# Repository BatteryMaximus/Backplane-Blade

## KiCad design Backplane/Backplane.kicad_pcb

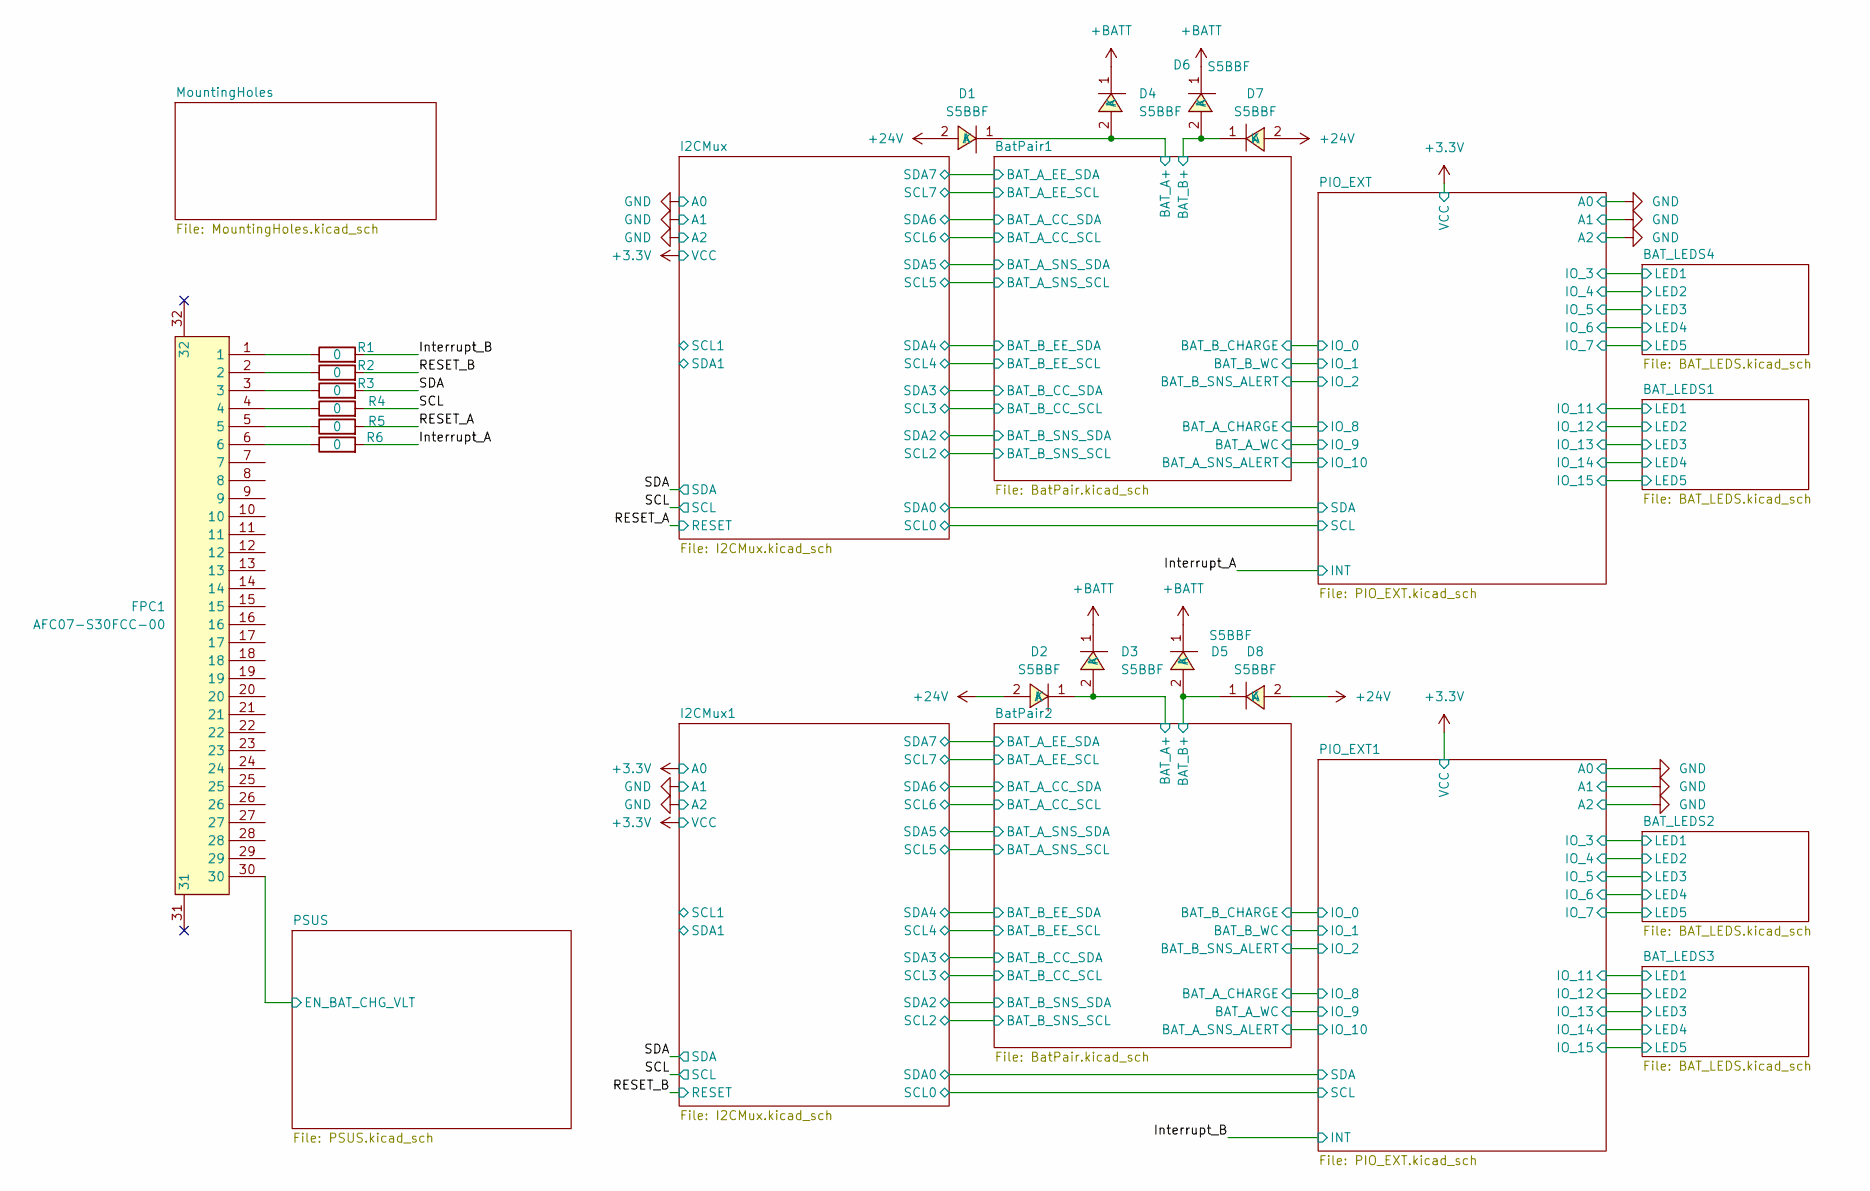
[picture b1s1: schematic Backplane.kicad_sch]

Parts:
D1, D2, D3, D4, D5, D6, D7, D8: S5BBF; SMBF_L4.3-W3.6-LS5.3-RD; LCSC Part C475750
FPC1: AFC07-S30FCC-00; FPC-SMD_P0.50-30P_LCSXJ-H2.0; LCSC Part C262218
R1, R2, R3, R4, R5, R6: 0; R_1206_3216Metric_Pad1.30x1.75mm_HandSolder

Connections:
+24V: D1.2 (A), D2.2 (A), D7.2 (A), D8.2 (A); also elsewhere on the board
+BATT: D3.1 (K), D4.1 (K), D5.1 (K), D6.1 (K); also elsewhere on the board
/BatPair1/BatMax - Female1/P+: D6.2 (A), D7.1 (K); also elsewhere on the board
/BatPair1/BatMax - Female/P+: D1.1 (K), D4.2 (A); also elsewhere on the board
/BatPair2/BatMax - Female1/P+: D5.2 (A), D8.1 (K); also elsewhere on the board
/BatPair2/BatMax - Female/P+: D2.1 (K), D3.2 (A); also elsewhere on the board
/Interrupt_A: R6.2; also elsewhere on the board
/Interrupt_B: R1.2; also elsewhere on the board
/PSUS/EN_BAT_CHG_VLT: FPC1.30; also elsewhere on the board
/RESET_A: R5.2; also elsewhere on the board
/RESET_B: R2.2; also elsewhere on the board
/SCL: R4.2; also elsewhere on the board
/SDA: R3.2; also elsewhere on the board
unnamed: FPC1.1, R1.1
unnamed: FPC1.2, R2.1
unnamed: FPC1.3, R3.1
unnamed: FPC1.4, R4.1
unnamed: FPC1.5, R5.1
unnamed: FPC1.6, R6.1

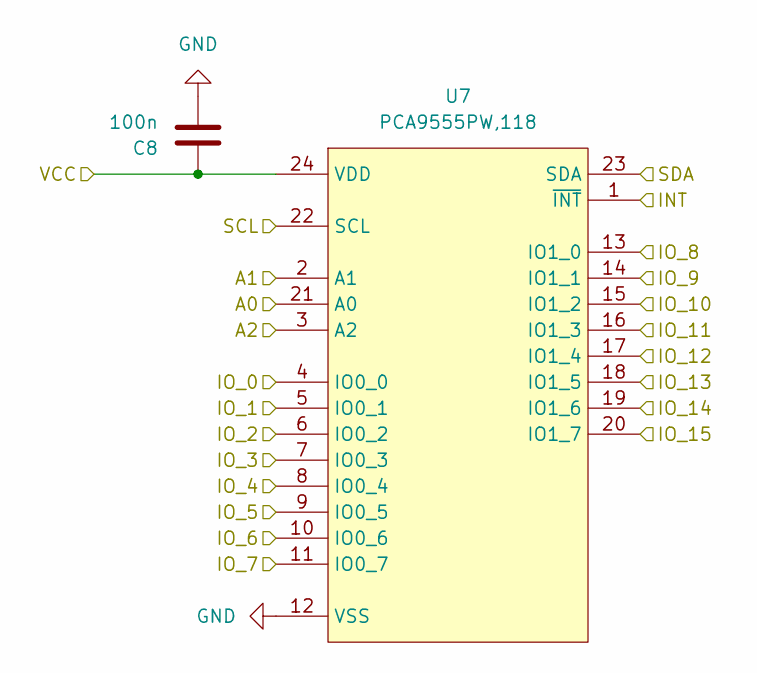
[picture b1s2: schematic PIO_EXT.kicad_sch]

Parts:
C8: 100n; R_1206_3216Metric_Pad1.30x1.75mm_HandSolder
U7: PCA9555PW,118; TSSOP-24_L7.8-W4.4-P0.65-LS6.4-BL; LCSC Part C128392

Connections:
+3.3V: C8.1, U7.24 (VDD); also elsewhere on the board
/BAT_LEDS1/LED1: U7.16 (IO1_3); also elsewhere on the board
/BAT_LEDS1/LED2: U7.17 (IO1_4); also elsewhere on the board
/BAT_LEDS1/LED3: U7.18 (IO1_5); also elsewhere on the board
/BAT_LEDS1/LED4: U7.19 (IO1_6); also elsewhere on the board
/BAT_LEDS1/LED5: U7.20 (IO1_7); also elsewhere on the board
/BAT_LEDS4/LED1: U7.7 (IO0_3); also elsewhere on the board
/BAT_LEDS4/LED2: U7.8 (IO0_4); also elsewhere on the board
/BAT_LEDS4/LED3: U7.9 (IO0_5); also elsewhere on the board
/BAT_LEDS4/LED4: U7.10 (IO0_6); also elsewhere on the board
/BAT_LEDS4/LED5: U7.11 (IO0_7); also elsewhere on the board
/BatPair1/BAT_A_CHARGE: U7.13 (IO1_0); also elsewhere on the board
/BatPair1/BAT_A_SNS_ALERT: U7.15 (IO1_2); also elsewhere on the board
/BatPair1/BAT_B_CHARGE: U7.4 (IO0_0); also elsewhere on the board
/BatPair1/BAT_B_SNS_ALERT: U7.6 (IO0_2); also elsewhere on the board
/BatPair1/BatMax - Female1/EEPROM_WC: U7.5 (IO0_1); also elsewhere on the board
/BatPair1/BatMax - Female/EEPROM_WC: U7.14 (IO1_1); also elsewhere on the board
/I2CMux/SCL0: U7.22 (SCL); also elsewhere on the board
/I2CMux/SDA0: U7.23 (SDA); also elsewhere on the board
/Interrupt_A: U7.1 (~INT); also elsewhere on the board
GND: C8.2, U7.2 (A1), U7.3 (A2), U7.12 (VSS), U7.21 (A0); also elsewhere on the board

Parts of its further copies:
C22: 100n; R_1206_3216Metric_Pad1.30x1.75mm_HandSolder
U20: PCA9555PW,118; TSSOP-24_L7.8-W4.4-P0.65-LS6.4-BL; LCSC Part C128392

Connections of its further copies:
+3.3V: C22.1, U20.24 (VDD); also elsewhere on the board
/BAT_LEDS2/LED1: U20.7 (IO0_3); also elsewhere on the board
/BAT_LEDS2/LED2: U20.8 (IO0_4); also elsewhere on the board
/BAT_LEDS2/LED3: U20.9 (IO0_5); also elsewhere on the board
/BAT_LEDS2/LED4: U20.10 (IO0_6); also elsewhere on the board
/BAT_LEDS2/LED5: U20.11 (IO0_7); also elsewhere on the board
/BAT_LEDS3/LED1: U20.16 (IO1_3); also elsewhere on the board
/BAT_LEDS3/LED2: U20.17 (IO1_4); also elsewhere on the board
/BAT_LEDS3/LED3: U20.18 (IO1_5); also elsewhere on the board
/BAT_LEDS3/LED4: U20.19 (IO1_6); also elsewhere on the board
/BAT_LEDS3/LED5: U20.20 (IO1_7); also elsewhere on the board
/BatPair2/BAT_A_CHARGE: U20.13 (IO1_0); also elsewhere on the board
/BatPair2/BAT_A_SNS_ALERT: U20.15 (IO1_2); also elsewhere on the board
/BatPair2/BAT_B_CHARGE: U20.4 (IO0_0); also elsewhere on the board
/BatPair2/BAT_B_SNS_ALERT: U20.6 (IO0_2); also elsewhere on the board
/BatPair2/BatMax - Female1/EEPROM_WC: U20.5 (IO0_1); also elsewhere on the board
/BatPair2/BatMax - Female/EEPROM_WC: U20.14 (IO1_1); also elsewhere on the board
/I2CMux1/SCL0: U20.22 (SCL); also elsewhere on the board
/I2CMux1/SDA0: U20.23 (SDA); also elsewhere on the board
/Interrupt_B: U20.1 (~INT); also elsewhere on the board
GND: C22.2, U20.2 (A1), U20.3 (A2), U20.12 (VSS), U20.21 (A0); also elsewhere on the board

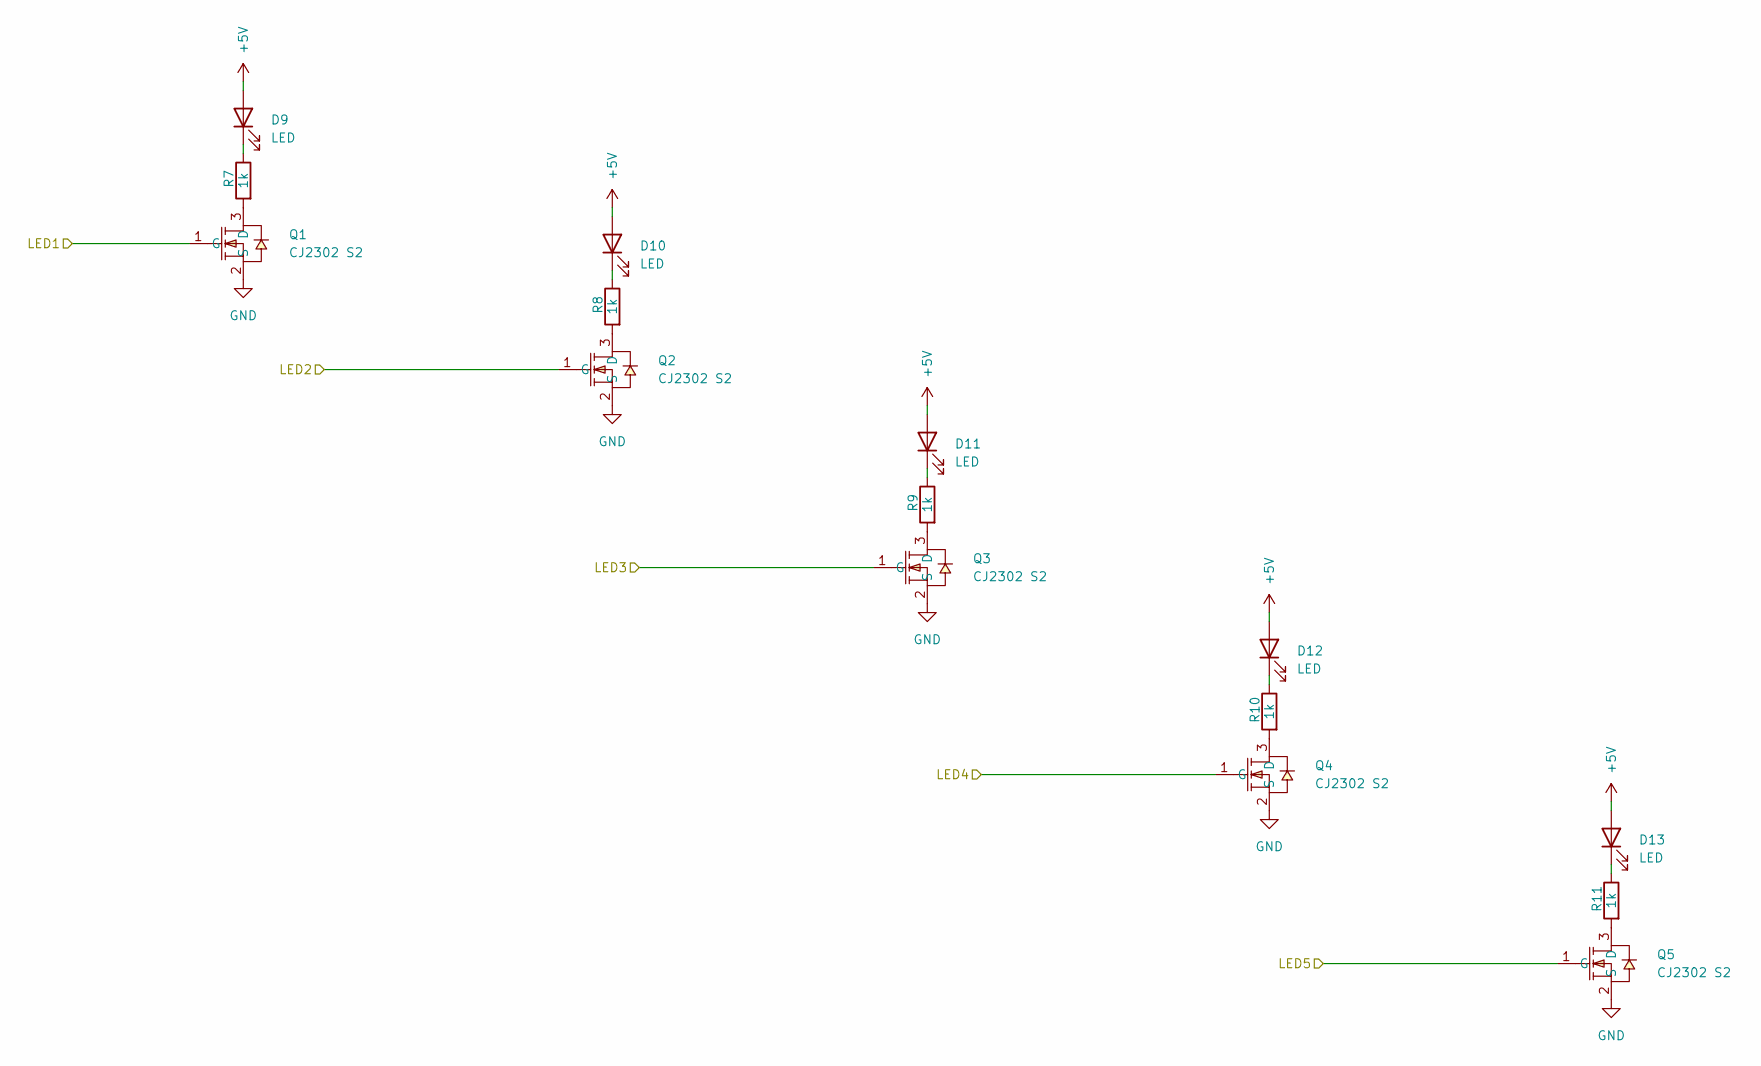
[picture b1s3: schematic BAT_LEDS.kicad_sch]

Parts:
D9, D10, D11, D12, D13: LED; LED_1206_3216Metric
Q1, Q2, Q3, Q4, Q5: CJ2302 S2; SOT-23-3_L3.0-W1.7-P0.95-LS2.9-BR; LCSC Part C8548
R7, R8, R9, R10, R11: 1k; R_1206_3216Metric_Pad1.30x1.75mm_HandSolder

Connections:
+5V: D9.2 (A), D10.2 (A), D11.2 (A), D12.2 (A), D13.2 (A); also elsewhere on the board
/BAT_LEDS1/LED1: Q1.1 (G); also elsewhere on the board
/BAT_LEDS1/LED2: Q2.1 (G); also elsewhere on the board
/BAT_LEDS1/LED3: Q3.1 (G); also elsewhere on the board
/BAT_LEDS1/LED4: Q4.1 (G); also elsewhere on the board
/BAT_LEDS1/LED5: Q5.1 (G); also elsewhere on the board
GND: Q1.2 (S), Q2.2 (S), Q3.2 (S), Q4.2 (S), Q5.2 (S); also elsewhere on the board
unnamed: D9.1 (K), R7.1
unnamed: D10.1 (K), R8.1
unnamed: D11.1 (K), R9.1
unnamed: D12.1 (K), R10.1
unnamed: D13.1 (K), R11.1
unnamed: Q1.3 (D), R7.2
unnamed: Q2.3 (D), R8.2
unnamed: Q3.3 (D), R9.2
unnamed: Q4.3 (D), R10.2
unnamed: Q5.3 (D), R11.2

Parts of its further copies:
D14, D15, D16, D17, D18, D19, D20, D21, D22, D23, D24, D25, D26, D27, D28: LED; LED_1206_3216Metric
Q6, Q7, Q8, Q9, Q10, Q11, Q12, Q13, Q14, Q15, Q18, Q19, Q20, Q21, Q22: CJ2302 S2; SOT-23-3_L3.0-W1.7-P0.95-LS2.9-BR; LCSC Part C8548
R12, R13, R14, R15, R16, R17, R18, R19, R20, R21, R48, R49, R50, R51, R52: 1k; R_1206_3216Metric_Pad1.30x1.75mm_HandSolder

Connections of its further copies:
+5V: D14.2 (A), D15.2 (A), D16.2 (A), D17.2 (A), D18.2 (A), D19.2 (A), D20.2 (A), D21.2 (A), D22.2 (A), D23.2 (A), D24.2 (A), D25.2 (A), D26.2 (A), D27.2 (A), D28.2 (A); also elsewhere on the board
/BAT_LEDS2/LED1: Q6.1 (G); also elsewhere on the board
/BAT_LEDS2/LED2: Q7.1 (G); also elsewhere on the board
/BAT_LEDS2/LED3: Q8.1 (G); also elsewhere on the board
/BAT_LEDS2/LED4: Q9.1 (G); also elsewhere on the board
/BAT_LEDS2/LED5: Q10.1 (G); also elsewhere on the board
/BAT_LEDS3/LED1: Q11.1 (G); also elsewhere on the board
/BAT_LEDS3/LED2: Q12.1 (G); also elsewhere on the board
/BAT_LEDS3/LED3: Q13.1 (G); also elsewhere on the board
/BAT_LEDS3/LED4: Q14.1 (G); also elsewhere on the board
/BAT_LEDS3/LED5: Q15.1 (G); also elsewhere on the board
/BAT_LEDS4/LED1: Q18.1 (G); also elsewhere on the board
/BAT_LEDS4/LED2: Q19.1 (G); also elsewhere on the board
/BAT_LEDS4/LED3: Q20.1 (G); also elsewhere on the board
/BAT_LEDS4/LED4: Q21.1 (G); also elsewhere on the board
/BAT_LEDS4/LED5: Q22.1 (G); also elsewhere on the board
GND: Q6.2 (S), Q7.2 (S), Q8.2 (S), Q9.2 (S), Q10.2 (S), Q11.2 (S), Q12.2 (S), Q13.2 (S), Q14.2 (S), Q15.2 (S), Q18.2 (S), Q19.2 (S), Q20.2 (S), Q21.2 (S), Q22.2 (S); also elsewhere on the board
unnamed: D14.1 (K), R12.1
unnamed: D15.1 (K), R13.1
unnamed: D16.1 (K), R14.1
unnamed: D17.1 (K), R15.1
unnamed: D18.1 (K), R16.1
unnamed: D19.1 (K), R17.1
unnamed: D20.1 (K), R18.1
unnamed: D21.1 (K), R19.1
unnamed: D22.1 (K), R20.1
unnamed: D23.1 (K), R21.1
unnamed: D24.1 (K), R48.1
unnamed: D25.1 (K), R49.1
unnamed: D26.1 (K), R50.1
unnamed: D27.1 (K), R51.1
unnamed: D28.1 (K), R52.1
unnamed: Q6.3 (D), R12.2
unnamed: Q7.3 (D), R13.2
unnamed: Q8.3 (D), R14.2
unnamed: Q9.3 (D), R15.2
unnamed: Q10.3 (D), R16.2
unnamed: Q11.3 (D), R17.2
unnamed: Q12.3 (D), R18.2
unnamed: Q13.3 (D), R19.2
unnamed: Q14.3 (D), R20.2
unnamed: Q15.3 (D), R21.2
unnamed: Q18.3 (D), R48.2
unnamed: Q19.3 (D), R49.2
unnamed: Q20.3 (D), R50.2
unnamed: Q21.3 (D), R51.2
unnamed: Q22.3 (D), R52.2

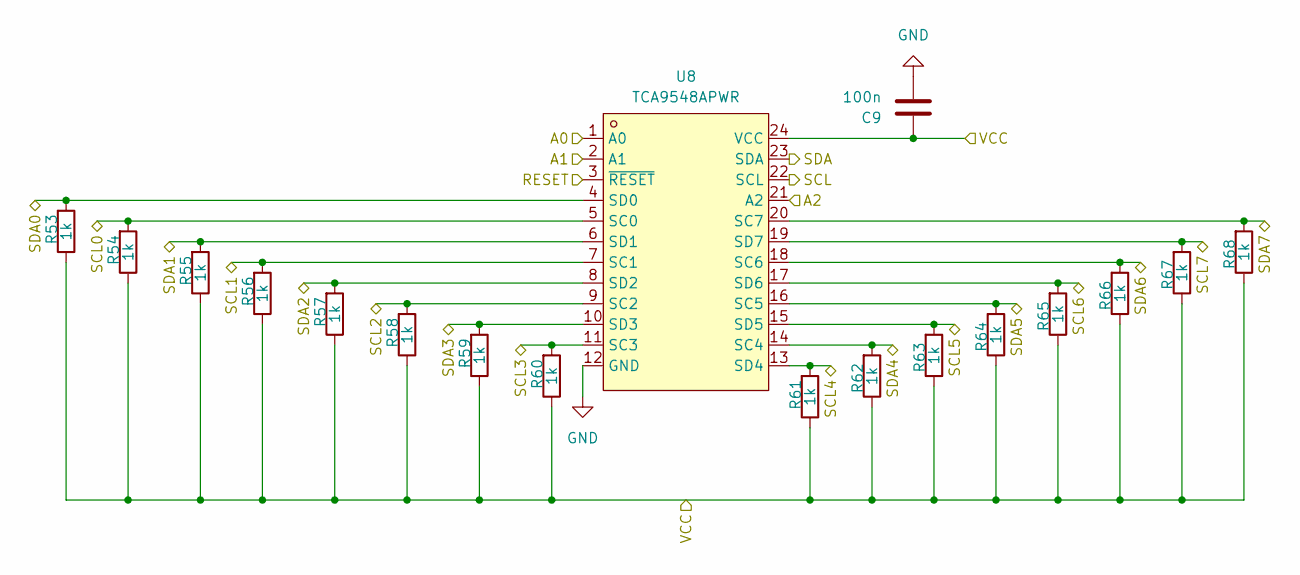
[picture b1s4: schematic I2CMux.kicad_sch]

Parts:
C9: 100n; R_1206_3216Metric_Pad1.30x1.75mm_HandSolder
R53, R54, R55, R56, R57, R58, R59, R60, R61, R62, R63, R64, R65, R66, R67, R68: 1k; R_1206_3216Metric_Pad1.30x1.75mm_HandSolder
U8: TCA9548APWR; TSSOP-24_L7.8-W4.4-P0.65-LS6.4-BL; LCSC Part C130026

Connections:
+3.3V: C9.1, R53.1, R54.1, R55.1, R56.1, R57.1, R58.1, R59.1, R60.1, R61.1, R62.1, R63.1, R64.1, R65.1, R66.1, R67.1, R68.1, U8.24 (VCC); also elsewhere on the board
/BatPair1/BAT_A_CC_SCL: R65.2, U8.17 (SD6); also elsewhere on the board
/BatPair1/BAT_A_CC_SDA: R66.2, U8.18 (SC6); also elsewhere on the board
/BatPair1/BAT_A_SNS_SCL: R63.2, U8.15 (SD5); also elsewhere on the board
/BatPair1/BAT_A_SNS_SDA: R64.2, U8.16 (SC5); also elsewhere on the board
/BatPair1/BAT_B_CC_SCL: R60.2, U8.11 (SC3); also elsewhere on the board
/BatPair1/BAT_B_CC_SDA: R59.2, U8.10 (SD3); also elsewhere on the board
/BatPair1/BAT_B_SNS_SCL: R58.2, U8.9 (SC2); also elsewhere on the board
/BatPair1/BAT_B_SNS_SDA: R57.2, U8.8 (SD2); also elsewhere on the board
/BatPair1/BatMax - Female1/SCL: R61.2, U8.13 (SD4); also elsewhere on the board
/BatPair1/BatMax - Female1/SDA: R62.2, U8.14 (SC4); also elsewhere on the board
/BatPair1/BatMax - Female/SCL: R67.2, U8.19 (SD7); also elsewhere on the board
/BatPair1/BatMax - Female/SDA: R68.2, U8.20 (SC7); also elsewhere on the board
/I2CMux/SCL0: R54.2, U8.5 (SC0); also elsewhere on the board
/I2CMux/SCL1: R56.2, U8.7 (SC1)
/I2CMux/SDA0: R53.2, U8.4 (SD0); also elsewhere on the board
/I2CMux/SDA1: R55.2, U8.6 (SD1)
/RESET_A: U8.3 (~RESET); also elsewhere on the board
/SCL: U8.22 (SCL); also elsewhere on the board
/SDA: U8.23 (SDA); also elsewhere on the board
GND: C9.2, U8.1 (A0), U8.2 (A1), U8.12 (GND), U8.21 (A2); also elsewhere on the board

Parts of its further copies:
C20: 100n; R_1206_3216Metric_Pad1.30x1.75mm_HandSolder
R83, R84, R85, R86, R87, R88, R89, R90, R91, R92, R93, R94, R95, R96, R97, R98: 1k; R_1206_3216Metric_Pad1.30x1.75mm_HandSolder
U18: TCA9548APWR; TSSOP-24_L7.8-W4.4-P0.65-LS6.4-BL; LCSC Part C130026

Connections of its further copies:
+3.3V: C20.1, R83.1, R84.1, R85.1, R86.1, R87.1, R88.1, R89.1, R90.1, R91.1, R92.1, R93.1, R94.1, R95.1, R96.1, R97.1, R98.1, U18.1 (A0), U18.24 (VCC); also elsewhere on the board
/BatPair2/BAT_A_CC_SCL: R95.2, U18.17 (SD6); also elsewhere on the board
/BatPair2/BAT_A_CC_SDA: R96.2, U18.18 (SC6); also elsewhere on the board
/BatPair2/BAT_A_SNS_SCL: R93.2, U18.15 (SD5); also elsewhere on the board
/BatPair2/BAT_A_SNS_SDA: R94.2, U18.16 (SC5); also elsewhere on the board
/BatPair2/BAT_B_CC_SCL: R90.2, U18.11 (SC3); also elsewhere on the board
/BatPair2/BAT_B_CC_SDA: R89.2, U18.10 (SD3); also elsewhere on the board
/BatPair2/BAT_B_SNS_SCL: R88.2, U18.9 (SC2); also elsewhere on the board
/BatPair2/BAT_B_SNS_SDA: R87.2, U18.8 (SD2); also elsewhere on the board
/BatPair2/BatMax - Female1/SCL: R91.2, U18.13 (SD4); also elsewhere on the board
/BatPair2/BatMax - Female1/SDA: R92.2, U18.14 (SC4); also elsewhere on the board
/BatPair2/BatMax - Female/SCL: R97.2, U18.19 (SD7); also elsewhere on the board
/BatPair2/BatMax - Female/SDA: R98.2, U18.20 (SC7); also elsewhere on the board
/I2CMux1/SCL0: R84.2, U18.5 (SC0); also elsewhere on the board
/I2CMux1/SCL1: R86.2, U18.7 (SC1)
/I2CMux1/SDA0: R83.2, U18.4 (SD0); also elsewhere on the board
/I2CMux1/SDA1: R85.2, U18.6 (SD1)
/RESET_B: U18.3 (~RESET); also elsewhere on the board
/SCL: U18.22 (SCL); also elsewhere on the board
/SDA: U18.23 (SDA); also elsewhere on the board
GND: C20.2, U18.2 (A1), U18.12 (GND), U18.21 (A2); also elsewhere on the board

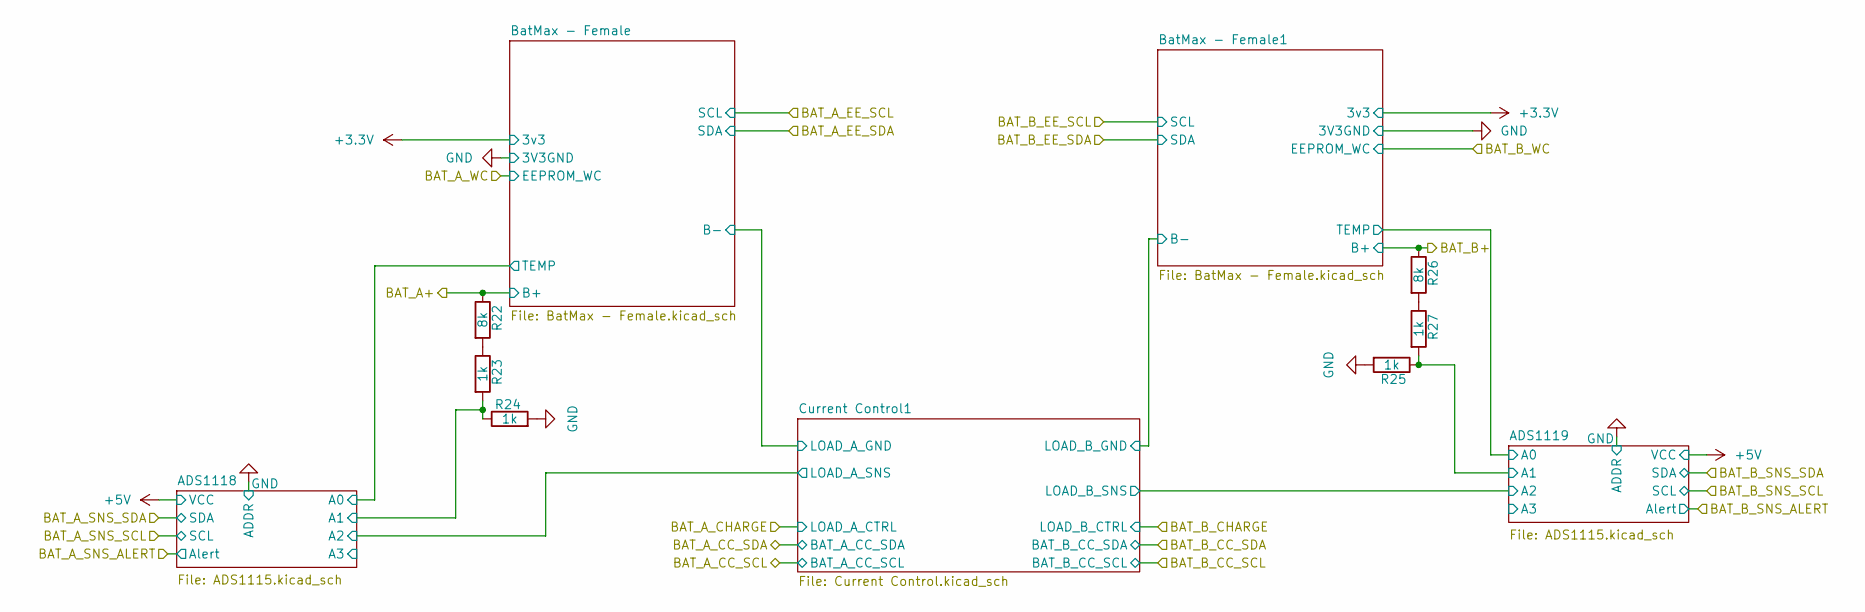
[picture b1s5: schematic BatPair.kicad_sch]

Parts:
R22, R26: 8k; R_1206_3216Metric_Pad1.30x1.75mm_HandSolder
R23, R24, R25, R27: 1k; R_1206_3216Metric_Pad1.30x1.75mm_HandSolder

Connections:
/BatPair2/ADS1118/A1: R23.2, R24.1; also elsewhere on the board
/BatPair2/ADS1119/A1: R25.1, R27.2; also elsewhere on the board
/BatPair2/BatMax - Female1/P+: R26.1; also elsewhere on the board
/BatPair2/BatMax - Female/P+: R22.1; also elsewhere on the board
GND: R24.2, R25.2; also elsewhere on the board
unnamed: R22.2, R23.1
unnamed: R26.2, R27.1

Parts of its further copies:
R28, R32: 8k; R_1206_3216Metric_Pad1.30x1.75mm_HandSolder
R29, R30, R31, R33: 1k; R_1206_3216Metric_Pad1.30x1.75mm_HandSolder

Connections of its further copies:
/BatPair1/ADS1118/A1: R29.2, R30.1; also elsewhere on the board
/BatPair1/ADS1119/A1: R31.1, R33.2; also elsewhere on the board
/BatPair1/BatMax - Female1/P+: R32.1; also elsewhere on the board
/BatPair1/BatMax - Female/P+: R28.1; also elsewhere on the board
GND: R30.2, R31.2; also elsewhere on the board
unnamed: R28.2, R29.1
unnamed: R32.2, R33.1

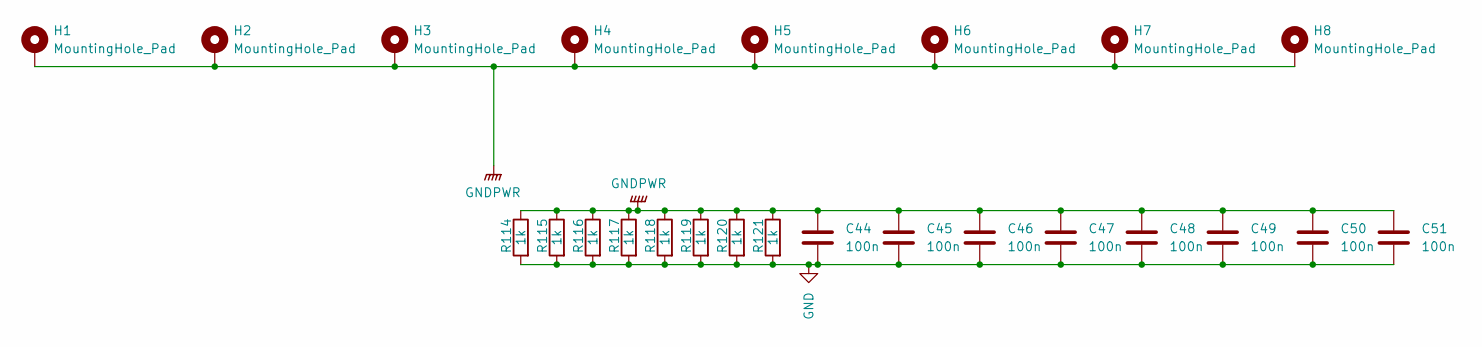
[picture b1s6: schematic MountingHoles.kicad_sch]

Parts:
C44, C45, C46, C47, C48, C49, C50, C51: 100n; R_1206_3216Metric_Pad1.30x1.75mm_HandSolder
H1, H2, H3, H4, H5, H6, H7, H8: MountingHole_Pad; MountingHole_3.2mm_M3_Pad_TopBottom
R114, R115, R116, R117, R118, R119, R120, R121: 1k; R_1206_3216Metric_Pad1.30x1.75mm_HandSolder

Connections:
GND: C44.2, C45.2, C46.2, C47.2, C48.2, C49.2, C50.2, C51.2, R114.2, R115.2, R116.2, R117.2, R118.2, R119.2, R120.2, R121.2; also elsewhere on the board
GNDPWR: C44.1, C45.1, C46.1, C47.1, C48.1, C49.1, C50.1, C51.1, H1.1, H2.1, H3.1, H4.1, H5.1, H6.1, H7.1, H8.1, R114.1, R115.1, R116.1, R117.1, R118.1, R119.1, R120.1, R121.1

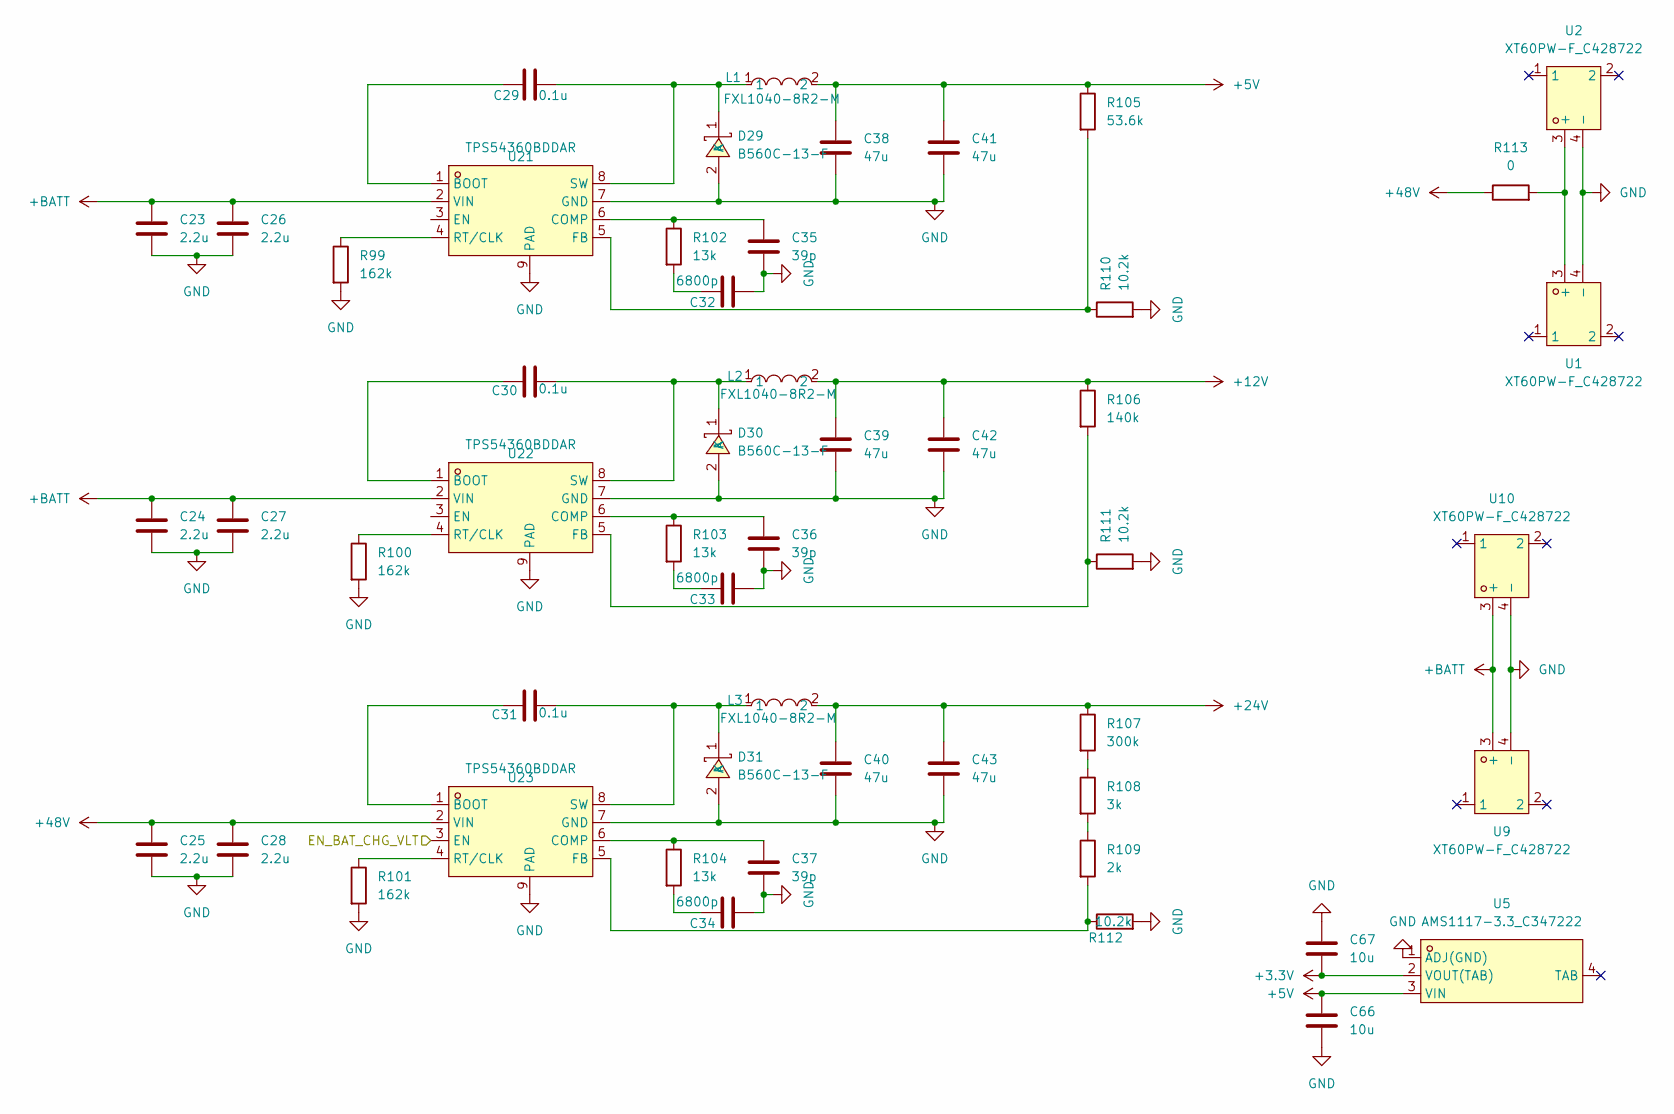
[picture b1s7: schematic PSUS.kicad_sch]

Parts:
C23, C24, C25, C26, C27, C28: 2.2u; C_1206_3216Metric; LCSC Part C170101
C29, C30, C31: 0.1u; C_1206_3216Metric; LCSC Part C56392
C32, C33, C34: 6800p; C_1206_3216Metric; LCSC Part C2760541
C35, C36, C37: 39p; C_1206_3216Metric; LCSC Part C5186878
C38, C39, C40, C41, C42, C43: 47u; C_1206_3216Metric; LCSC Part C94034
C66, C67: 10u; C_1206_3216Metric; LCSC Part C94034
D29, D30, D31: B560C-13-F; SMC_L7.1-W6.2-LS8.1-RD; LCSC Part C85100
L1, L2, L3: FXL1040-8R2-M; IND-SMD_L11.5-W10.0_FXL1040; LCSC Part C167232
R99, R100, R101: 162k; R_1206_3216Metric_Pad1.30x1.75mm_HandSolder; LCSC Part C22815
R102, R103, R104: 13k; R_1206_3216Metric_Pad1.30x1.75mm_HandSolder; LCSC Part C445658
R105: 53.6k; R_1206_3216Metric_Pad1.30x1.75mm_HandSolder; LCSC Part C21398
R106: 140k; R_1206_3216Metric_Pad1.30x1.75mm_HandSolder; LCSC Part C21398
R107: 300k; R_1206_3216Metric_Pad1.30x1.75mm_HandSolder; LCSC Part C21398
R108: 3k; R_1206_3216Metric_Pad1.30x1.75mm_HandSolder; LCSC Part C21398
R109: 2k; R_1206_3216Metric_Pad1.30x1.75mm_HandSolder; LCSC Part C21398
R110, R111, R112: 10.2k; R_1206_3216Metric_Pad1.30x1.75mm_HandSolder; LCSC Part C21398
R113: 0; R_1206_3216Metric_Pad1.30x1.75mm_HandSolder; LCSC Part C21398
U1, U2, U9, U10: XT60PW-F_C428722; TH_2P-XT60PW-F; LCSC Part C428722
U5: AMS1117-3.3_C347222; SOT-223-4_L6.5-W3.5-P2.30-LS7.0-BR; LCSC Part C347222
U21, U22, U23: TPS54360BDDAR; SOIC-8_L5.0-W4.0-P1.27-LS6.0-BL-EP2.0; LCSC Part C524806

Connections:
+3.3V: C67.2, U5.2 (VOUT(TAB)); also elsewhere on the board
+5V: C38.1, C41.1, C66.1, L1.2, R105.1, U5.3 (VIN); also elsewhere on the board
+12V: C39.1, C42.1, L2.2, R106.1; also elsewhere on the board
+24V: C40.1, C43.1, L3.2, R107.1; also elsewhere on the board
+48V: C25.1, C28.1, R113.1, U23.2 (VIN)
+BATT: C23.1, C24.1, C26.1, C27.1, U9.3 (+), U10.3 (+), U21.2 (VIN), U22.2 (VIN); also elsewhere on the board
/PSUS/EN_BAT_CHG_VLT: U23.3 (EN); also elsewhere on the board
GND: C23.2, C24.2, C25.2, C26.2, C27.2, C28.2, C32.2, C33.2, C34.2, C35.2, C36.2, C37.2, C38.2, C39.2, C40.2, C41.2, C42.2, C43.2, C66.2, C67.1, D29.2 (A), D30.2 (A), D31.2 (A), R99.2, R100.2, R101.2, R110.2, R111.2, R112.2, U1.4 (-), U2.4 (-), U5.1 (ADJ(GND)), U9.4 (-), U10.4 (-), U21.7 (GND), U21.9 (PAD), U22.7 (GND), U22.9 (PAD), U23.7 (GND), U23.9 (PAD); also elsewhere on the board
unnamed: C32.1, R102.2
unnamed: C33.1, R103.2
unnamed: C34.1, R104.2
unnamed: C29.2, D29.1 (K), L1.1, U21.8 (SW)
unnamed: C30.2, D30.1 (K), L2.1, U22.8 (SW)
unnamed: C31.2, D31.1 (K), L3.1, U23.8 (SW)
unnamed: R107.2, R108.1
unnamed: R108.2, R109.1
unnamed: R113.2, U1.3 (+), U2.3 (+)
unnamed: C29.1, U21.1 (BOOT)
unnamed: C35.1, R102.1, U21.6 (COMP)
unnamed: R105.2, R110.1, U21.5 (FB)
unnamed: R99.1, U21.4 (RT/CLK)
unnamed: C30.1, U22.1 (BOOT)
unnamed: C36.1, R103.1, U22.6 (COMP)
unnamed: R106.2, R111.1, U22.5 (FB)
unnamed: R100.1, U22.4 (RT/CLK)
unnamed: C31.1, U23.1 (BOOT)
unnamed: C37.1, R104.1, U23.6 (COMP)
unnamed: R109.2, R112.1, U23.5 (FB)
unnamed: R101.1, U23.4 (RT/CLK)

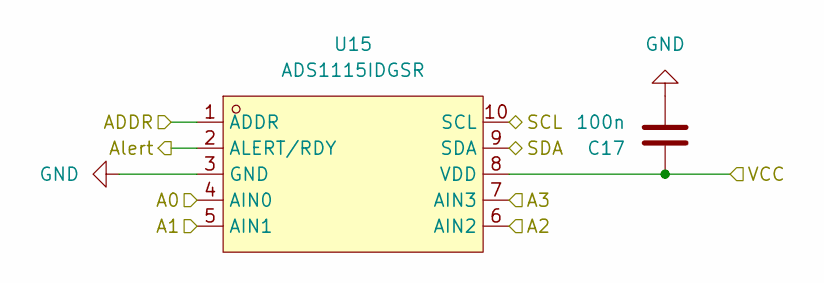
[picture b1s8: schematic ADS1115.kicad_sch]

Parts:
C17: 100n; R_1206_3216Metric_Pad1.30x1.75mm_HandSolder
U15: ADS1115IDGSR; MSOP-10_L3.0-W3.0-P0.50-LS5.0-BL; LCSC Part C37593

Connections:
+5V: C17.1, U15.8 (VDD); also elsewhere on the board
/BatPair2/ADS1118/A1: U15.5 (AIN1); also elsewhere on the board
/BatPair2/ADS1118/A2: U15.6 (AIN2); also elsewhere on the board
/BatPair2/ADS1118/A3: U15.7 (AIN3)
/BatPair2/BAT_A_SNS_ALERT: U15.2 (ALERT/RDY); also elsewhere on the board
/BatPair2/BAT_A_SNS_SCL: U15.10 (SCL); also elsewhere on the board
/BatPair2/BAT_A_SNS_SDA: U15.9 (SDA); also elsewhere on the board
/BatPair2/BatMax - Female/TEMP: U15.4 (AIN0); also elsewhere on the board
GND: C17.2, U15.1 (ADDR), U15.3 (GND); also elsewhere on the board

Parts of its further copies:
C18, C19, C21: 100n; R_1206_3216Metric_Pad1.30x1.75mm_HandSolder
U16, U17, U19: ADS1115IDGSR; MSOP-10_L3.0-W3.0-P0.50-LS5.0-BL; LCSC Part C37593

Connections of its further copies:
+5V: C18.1, C19.1, C21.1, U16.8 (VDD), U17.8 (VDD), U19.8 (VDD); also elsewhere on the board
/BatPair1/ADS1118/A1: U17.5 (AIN1); also elsewhere on the board
/BatPair1/ADS1118/A2: U17.6 (AIN2); also elsewhere on the board
/BatPair1/ADS1118/A3: U17.7 (AIN3)
/BatPair1/ADS1119/A1: U19.5 (AIN1); also elsewhere on the board
/BatPair1/ADS1119/A2: U19.6 (AIN2); also elsewhere on the board
/BatPair1/ADS1119/A3: U19.7 (AIN3)
/BatPair1/BAT_A_SNS_ALERT: U17.2 (ALERT/RDY); also elsewhere on the board
/BatPair1/BAT_A_SNS_SCL: U17.10 (SCL); also elsewhere on the board
/BatPair1/BAT_A_SNS_SDA: U17.9 (SDA); also elsewhere on the board
/BatPair1/BAT_B_SNS_ALERT: U19.2 (ALERT/RDY); also elsewhere on the board
/BatPair1/BAT_B_SNS_SCL: U19.10 (SCL); also elsewhere on the board
/BatPair1/BAT_B_SNS_SDA: U19.9 (SDA); also elsewhere on the board
/BatPair1/BatMax - Female1/TEMP: U19.4 (AIN0); also elsewhere on the board
/BatPair1/BatMax - Female/TEMP: U17.4 (AIN0); also elsewhere on the board
/BatPair2/ADS1119/A1: U16.5 (AIN1); also elsewhere on the board
/BatPair2/ADS1119/A2: U16.6 (AIN2); also elsewhere on the board
/BatPair2/ADS1119/A3: U16.7 (AIN3)
/BatPair2/BAT_B_SNS_ALERT: U16.2 (ALERT/RDY); also elsewhere on the board
/BatPair2/BAT_B_SNS_SCL: U16.10 (SCL); also elsewhere on the board
/BatPair2/BAT_B_SNS_SDA: U16.9 (SDA); also elsewhere on the board
/BatPair2/BatMax - Female1/TEMP: U16.4 (AIN0); also elsewhere on the board
GND: C18.2, C19.2, C21.2, U16.1 (ADDR), U16.3 (GND), U17.1 (ADDR), U17.3 (GND), U19.1 (ADDR), U19.3 (GND); also elsewhere on the board

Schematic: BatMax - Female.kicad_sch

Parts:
J1: Bus_PCI_Express_x1; CONN-TH_36P-P1.00-V_3183-XXXXXPXT

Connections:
+3.3V: J1.B1; also elsewhere on the board
/BatPair1/BatMax - Female1/EEPROM_WC: J1.B3; also elsewhere on the board
/BatPair1/BatMax - Female1/P+: J1.B6, J1.B7, J1.B8, J1.B9, J1.B10, J1.B11, J1.B12, J1.B13, J1.B14, J1.B15, J1.B16, J1.B17, J1.B18; also elsewhere on the board
/BatPair1/BatMax - Female1/P-: J1.A6, J1.A7, J1.A8, J1.A9, J1.A10, J1.A11, J1.A12, J1.A13, J1.A14, J1.A15, J1.A16, J1.A17, J1.A18; also elsewhere on the board
/BatPair1/BatMax - Female1/SCL: J1.A2; also elsewhere on the board
/BatPair1/BatMax - Female1/SDA: J1.B2; also elsewhere on the board
/BatPair1/BatMax - Female1/TEMP: J1.A3; also elsewhere on the board
GND: J1.A1; also elsewhere on the board

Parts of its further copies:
J2, J3, J4: Bus_PCI_Express_x1; CONN-TH_36P-P1.00-V_3183-XXXXXPXT

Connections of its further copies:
+3.3V: J2.B1, J3.B1, J4.B1; also elsewhere on the board
/BatPair1/BatMax - Female/EEPROM_WC: J2.B3; also elsewhere on the board
/BatPair1/BatMax - Female/P+: J2.B6, J2.B7, J2.B8, J2.B9, J2.B10, J2.B11, J2.B12, J2.B13, J2.B14, J2.B15, J2.B16, J2.B17, J2.B18; also elsewhere on the board
/BatPair1/BatMax - Female/P-: J2.A6, J2.A7, J2.A8, J2.A9, J2.A10, J2.A11, J2.A12, J2.A13, J2.A14, J2.A15, J2.A16, J2.A17, J2.A18; also elsewhere on the board
/BatPair1/BatMax - Female/SCL: J2.A2; also elsewhere on the board
/BatPair1/BatMax - Female/SDA: J2.B2; also elsewhere on the board
/BatPair1/BatMax - Female/TEMP: J2.A3; also elsewhere on the board
/BatPair2/BatMax - Female1/EEPROM_WC: J4.B3; also elsewhere on the board
/BatPair2/BatMax - Female1/P+: J4.B6, J4.B7, J4.B8, J4.B9, J4.B10, J4.B11, J4.B12, J4.B13, J4.B14, J4.B15, J4.B16, J4.B17, J4.B18; also elsewhere on the board
/BatPair2/BatMax - Female1/P-: J4.A6, J4.A7, J4.A8, J4.A9, J4.A10, J4.A11, J4.A12, J4.A13, J4.A14, J4.A15, J4.A16, J4.A17, J4.A18; also elsewhere on the board
/BatPair2/BatMax - Female1/SCL: J4.A2; also elsewhere on the board
/BatPair2/BatMax - Female1/SDA: J4.B2; also elsewhere on the board
/BatPair2/BatMax - Female1/TEMP: J4.A3; also elsewhere on the board
/BatPair2/BatMax - Female/EEPROM_WC: J3.B3; also elsewhere on the board
/BatPair2/BatMax - Female/P+: J3.B6, J3.B7, J3.B8, J3.B9, J3.B10, J3.B11, J3.B12, J3.B13, J3.B14, J3.B15, J3.B16, J3.B17, J3.B18; also elsewhere on the board
/BatPair2/BatMax - Female/P-: J3.A6, J3.A7, J3.A8, J3.A9, J3.A10, J3.A11, J3.A12, J3.A13, J3.A14, J3.A15, J3.A16, J3.A17, J3.A18; also elsewhere on the board
/BatPair2/BatMax - Female/SCL: J3.A2; also elsewhere on the board
/BatPair2/BatMax - Female/SDA: J3.B2; also elsewhere on the board
/BatPair2/BatMax - Female/TEMP: J3.A3; also elsewhere on the board
GND: J2.A1, J3.A1, J4.A1; also elsewhere on the board

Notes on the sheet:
3v3 -----
----- TEMP
50k Resistor
3v3GND -----
50k(3800) NTC Thermistor
Thermistor Connection on Battery
